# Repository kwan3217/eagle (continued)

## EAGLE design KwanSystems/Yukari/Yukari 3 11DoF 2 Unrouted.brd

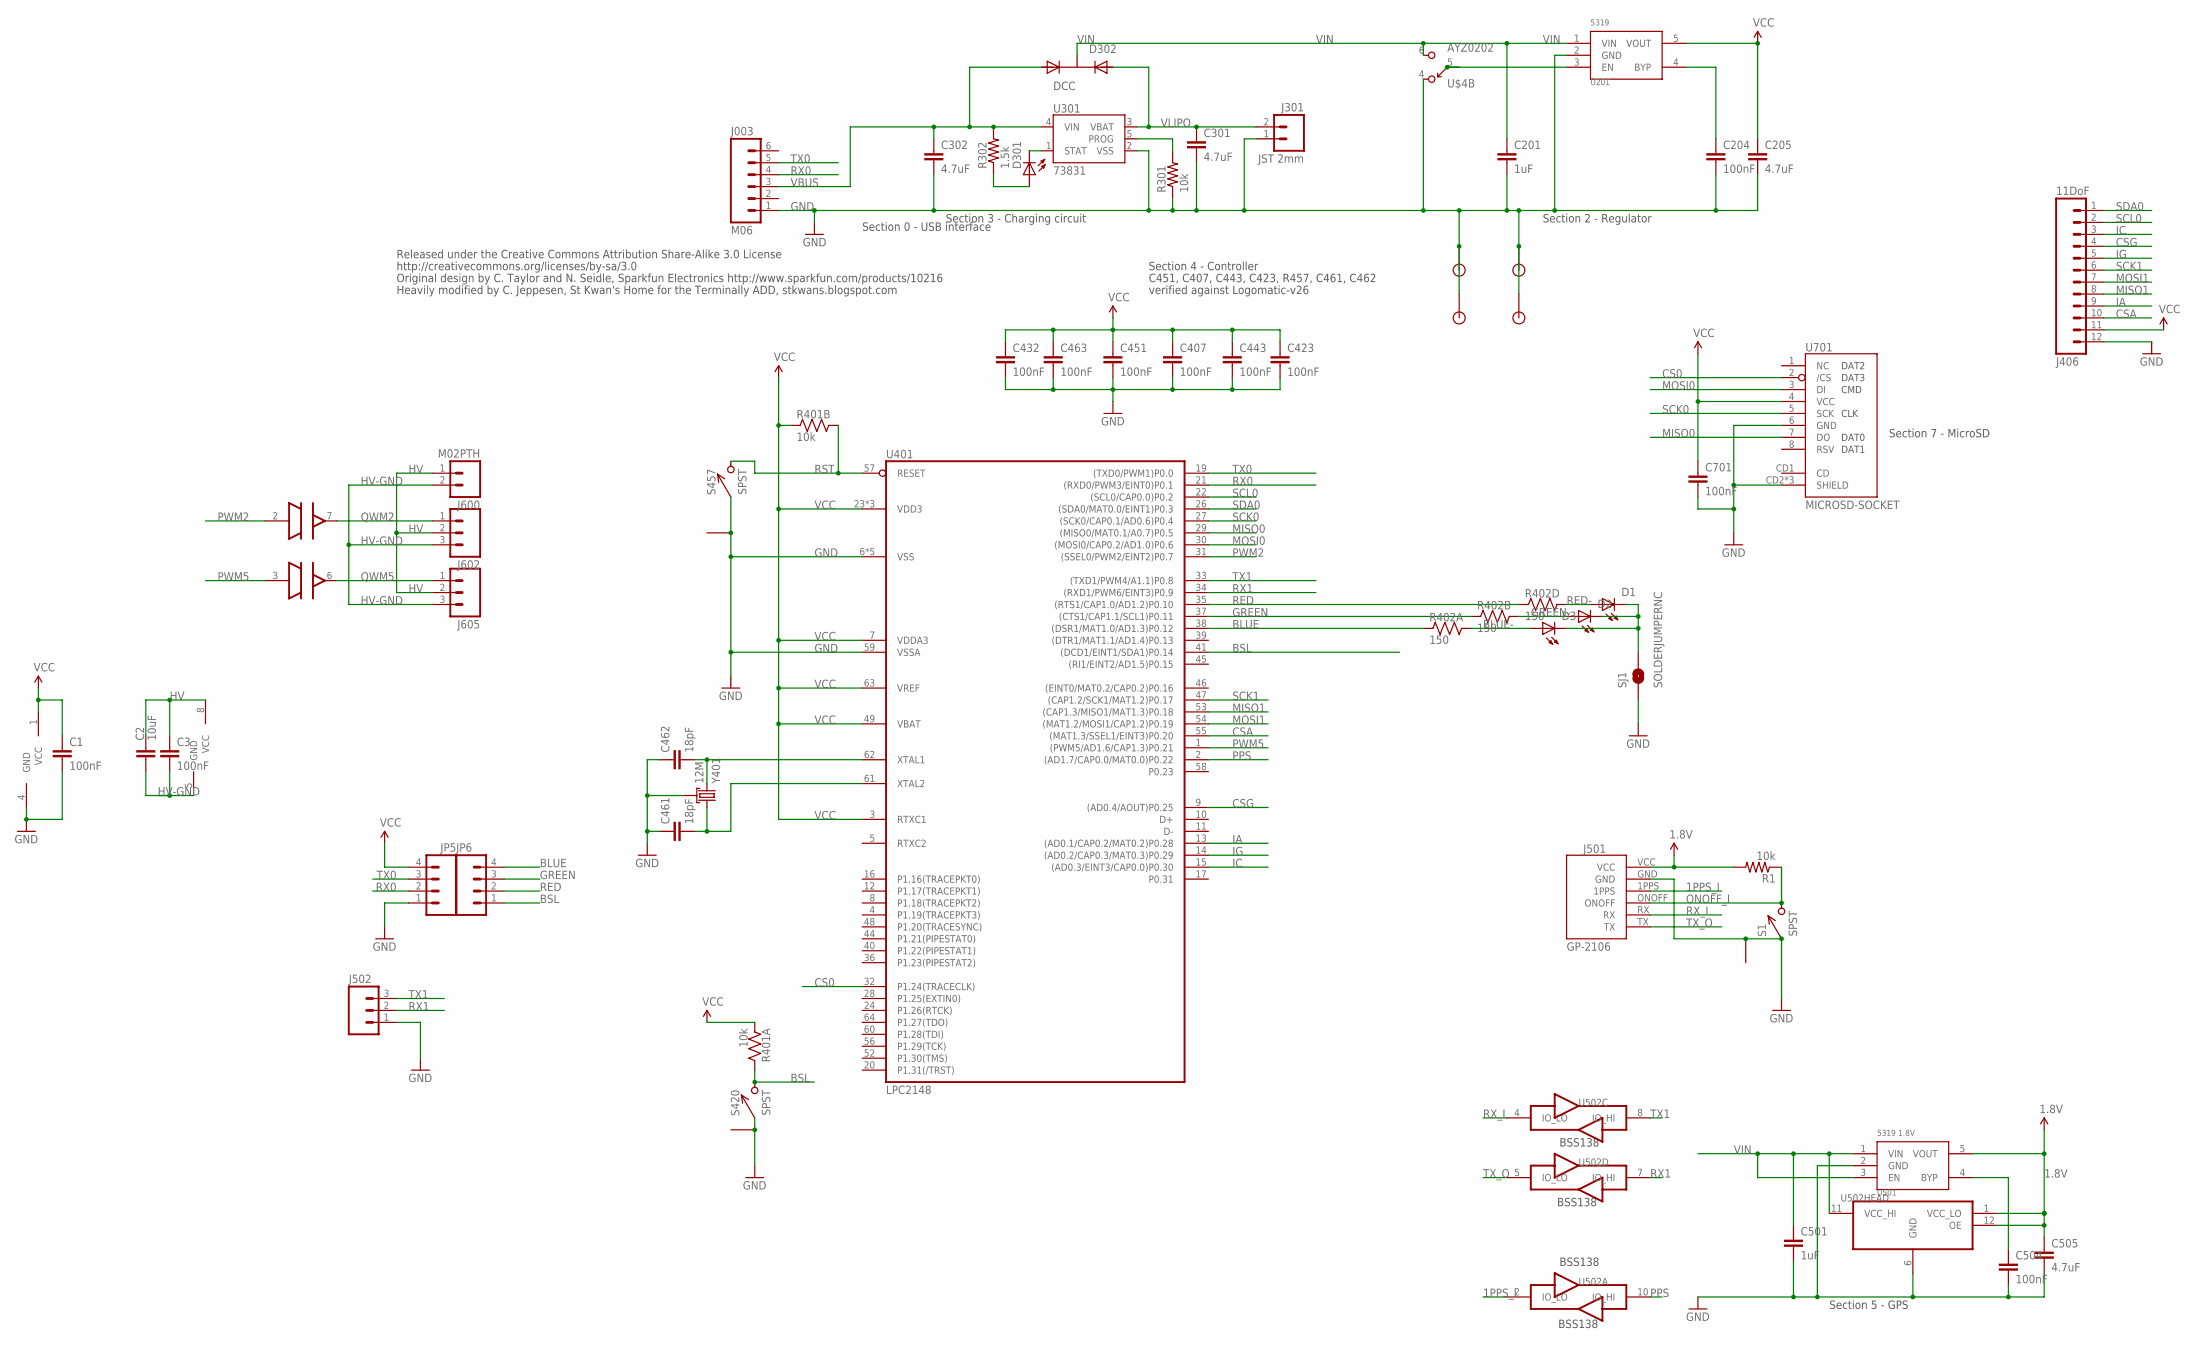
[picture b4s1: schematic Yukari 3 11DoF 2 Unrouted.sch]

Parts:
C1, C3, C204, C407, C423, C432, C443, C451, C463, C701: 100nF; 0402-CAP
C2: 10uF; 0603-CAP; DIGIKEY 445-7486-1-ND
C201: 1uF; 0402-CAP
C205, C301, C302: 4.7uF; 0402-CAP
C461, C462: 18pF; 0402-CAP
C501: 1uF; 0402-CAP; DIGIKEY 445-4114-1-ND
C504: 100nF; 0402-CAP; DIGIKEY 445-1265-1-ND
C505: 4.7uF; 0402-CAP; DIGIKEY 445-7395-1-ND
D1, D301: RED; LED-0603
D2: GREEN; LED-0603
D3: BLUE; LED-0603
D302: DCC; SOT-23-3
J003: M06; 1X06
J301: JST 2mm; JST-2-SMD
J406: 11DoF; 1X12
J501: GP-2106
J502, J602, J605: M03PTH; 1X03
J600: M02PTH; 1X02
JP1, JP2, JP3, JP4: STANDOFF
JP5, JP6: M04PTH; 1X04
R1, R301: 10k; 0402-RES
R302: 1.5k; 0402-RES
R401: 10k; CRA02
R402: 150; CRA04
S1, S420, S457: SPST; B3U-1100P
SJ1: SOLDERJUMPERNC; SJ_2S
U201: 5319; SOT-23-5
U301: 73831; SOT23-5
U401: LPC2148; LQFP64
U501: 5319 1.8V; SOT-23-5; DIGIKEY 576-1910-1-ND
U502: TXB0104RUT; R-PUQFN-N12
U600: ADUM3221; SO8N
U701: MICROSD-SOCKET; MICROSD-SOCKET-PP
U$4: AYZ0202
Y401: 12M; CRYSTAL_SMD

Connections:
1.8V: C505.1, J501.VCC, R1.2, U501.5 (VOUT), U502.1 (VCC_LO), U502.12 (OE)
1PPS_I: J501.1PPS, U502.2 (IO_LO)
BLUE: JP6.4, R402.1, U401.38 ((DSR1/MAT1.0/AD1.3)P0.12)
BLUE-: D3.A, R402.8 (2)
BSL: JP6.1, R401.4 (2), S420.P$2 (2), U401.41 ((DCD1/EINT1/SDA1)P0.14)
CHG_PROG: R301.2, U301.5 (PROG)
CS0: U401.32 (P1.24(TRACECLK)), U701.2 (/CS)
CSA: J406.10, U401.55 ((MAT1.3/SSEL1/EINT3)P0.20)
CSG: J406.4, U401.9 ((AD0.4/AOUT)P0.25)
EN: U201.3 (EN), U$4.5
GND: C1.2, C201.2, C204.2, C205.2, C301.2, C302.2, C407.2, C423.2, C432.2, C443.2, C451.2, C461.1, C462.1, C463.2, C501.2, C504.2, C505.2, C701.2, J003.1, J301.1, J406.12, J501.GND, J502.1, JP1.P$1, JP2.P$1, JP3.P$1, JP4.P$1, JP5.1, R301.1, S1.P$1 (1), S1.P$3 (1), S420.P$1 (1), S420.P$3 (1), S457.P$1 (1), S457.P$3 (1), SJ1.1, U201.2 (GND), U301.2 (VSS), U401.6 (VSS), U401.18 (VSS), U401.25 (VSS), U401.42 (VSS), U401.50 (VSS), U401.59 (VSSA), U501.2 (GND), U502.6 (GND), U600.4 (GND), U701.6 (GND), U701.CD2 (SHIELD), U701.GND1 (SHIELD), U701.GND3 (SHIELD), U$4.4, Y401.2 (GND), Y401.4 (GND)
GREEN: JP6.3, R402.2 (1), U401.37 ((CTS1/CAP1.1/SCL1)P0.11)
GREEN-: D2.A, R402.7 (2)
HV: C2.1, C3.1, J600.1, J602.2, J605.2, U600.8 (VCC)
HV-GND: C2.2, C3.2, J600.2, J602.3, J605.3, U600.5 (GND)
IA: J406.9, U401.13 ((AD0.1/CAP0.2/MAT0.2)P0.28)
IC: J406.3, U401.15 ((AD0.3/EINT3/CAP0.0)P0.30)
IG: J406.5, U401.14 ((AD0.2/CAP0.3/MAT0.3)P0.29)
MISO0: U401.29 ((MISO0/MAT0.1/A0.7)P0.5), U701.7 (DO)
MISO1: J406.8, U401.53 ((CAP1.3/MISO1/MAT1.3)P0.18)
MOSI0: U401.30 ((MOSI0/CAP0.2/AD1.0)P0.6), U701.3 (DI)
MOSI1: J406.7, U401.54 ((MAT1.2/MOSI1/CAP1.2)P0.19)
unnamed: D1.C, D2.C, D3.C, SJ1.2
unnamed: C504.1, U501.4 (BYP)
unnamed: C204.1, U201.4 (BYP)
ONOFF_I: J501.ONOFF, R1.1, S1.P$2 (2)
PPS: U401.2 ((AD1.7/CAP0.0/MAT0.0)P0.22), U502.10 (IO_HI)
PWM2: U401.31 ((SSEL0/PWM2/EINT2)P0.7), U600.2 (IN)
PWM5: U401.1 ((PWM5/AD1.6/CAP1.3)P0.21), U600.3 (IN)
QWM2: J602.1, U600.7 (OUT)
QWM5: J605.1, U600.6 (OUT)
RED: JP6.2, R402.4 (1), U401.35 ((RTS1/CAP1.0/AD1.2)P0.10)
RED-: D1.A, R402.5 (2)
RST: R401.3 (2), S457.P$2 (2), U401.57 (RESET)
RX0: J003.4, JP5.2, U401.21 ((RXD0/PWM3/EINT0)P0.1)
RX1: J502.2, U401.34 ((RXD1/PWM6/EINT3)P0.9), U502.7 (IO_HI)
RX_I: J501.RX, U502.4 (IO_LO)
SCK0: U401.27 ((SCK0/CAP0.1/AD0.6)P0.4), U701.5 (SCK)
SCK1: J406.6, U401.47 ((CAP1.2/SCK1/MAT1.2)P0.17)
SCL0: J406.2, U401.22 ((SCL0/CAP0.0)P0.2)
SDA0: J406.1, U401.26 ((SDA0/MAT0.0/EINT1)P0.3)
STAT+: D301.A, R302.1
STAT-: D301.C, U301.1 (STAT)
TX0: J003.5, JP5.3, U401.19 ((TXD0/PWM1)P0.0)
TX1: J502.3, U401.33 ((TXD1/PWM4/A1.1)P0.8), U502.8 (IO_HI)
TX_O: J501.TX, U502.5 (IO_LO)
VBUS: C302.1, D302.1 (A1), J003.3, R302.2, U301.4 (VIN)
VCC: C1.1, C205.1, C407.1, C423.1, C432.1, C443.1, C451.1, C463.1, C701.1, J406.11, JP5.4, R401.1, R401.2 (1), U201.5 (VOUT), U401.3 (RTXC1), U401.7 (VDDA3), U401.23 (VDD3), U401.43 (VDD3), U401.49 (VBAT), U401.51 (VDD3), U401.63 (VREF), U600.1 (VCC), U701.4 (VCC)
VIN: C201.1, C501.1, D302.3 (K), U201.1 (VIN), U501.1 (VIN), U501.3 (EN), U502.11 (VCC_HI), U$4.6
VLIPO: C301.1, D302.2 (A2), J301.2, U301.3 (VBAT)
XTAL1: C462.2, U401.62 (XTAL1), Y401.3 (2)
XTAL2: C461.2, U401.61 (XTAL2), Y401.1

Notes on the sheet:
Section 4 - Controller
Section 7 - MicroSD
C451, C407, C443, C423, R457, C461, C462
verified against Logomatic-v26
Section 2 - Regulator
Section 3 - Charging circuit
Section 0 - USB interface
Released under the Creative Commons Attribution Share-Alike 3.0 License
http://creativecommons.org/licenses/by-sa/3.0
Original design by C. Taylor and N. Seidle, Sparkfun Electronics http://www.sparkfun.com/products/10216
Heavily modified by C. Jeppesen, St Kwan's Home for the Terminally ADD, stkwans.blogspot.com
BSS138
Section 5 - GPS

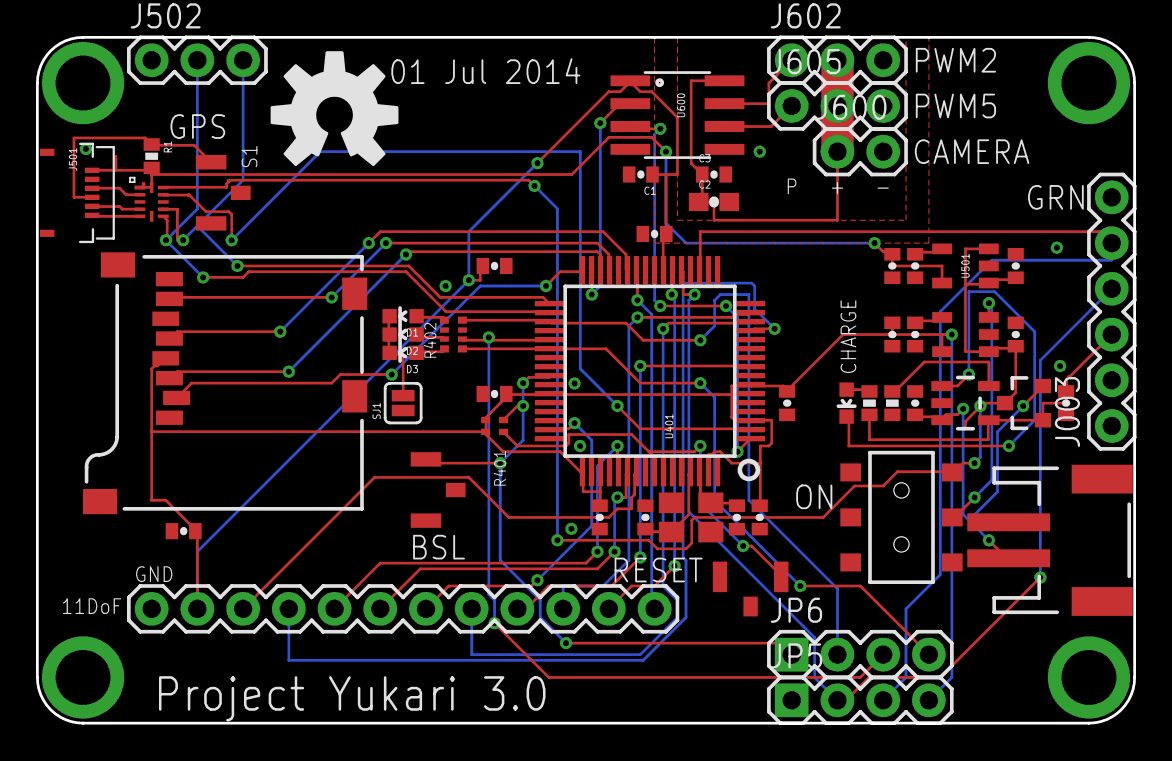
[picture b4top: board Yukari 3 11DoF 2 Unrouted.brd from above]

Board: 2 copper layers, 61.0 x 38.1 mm, 59 parts (1 on the bottom side), 52 nets.

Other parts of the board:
U$1: KWAN_CIRCLE
U$2: OSHW-LOGO-L

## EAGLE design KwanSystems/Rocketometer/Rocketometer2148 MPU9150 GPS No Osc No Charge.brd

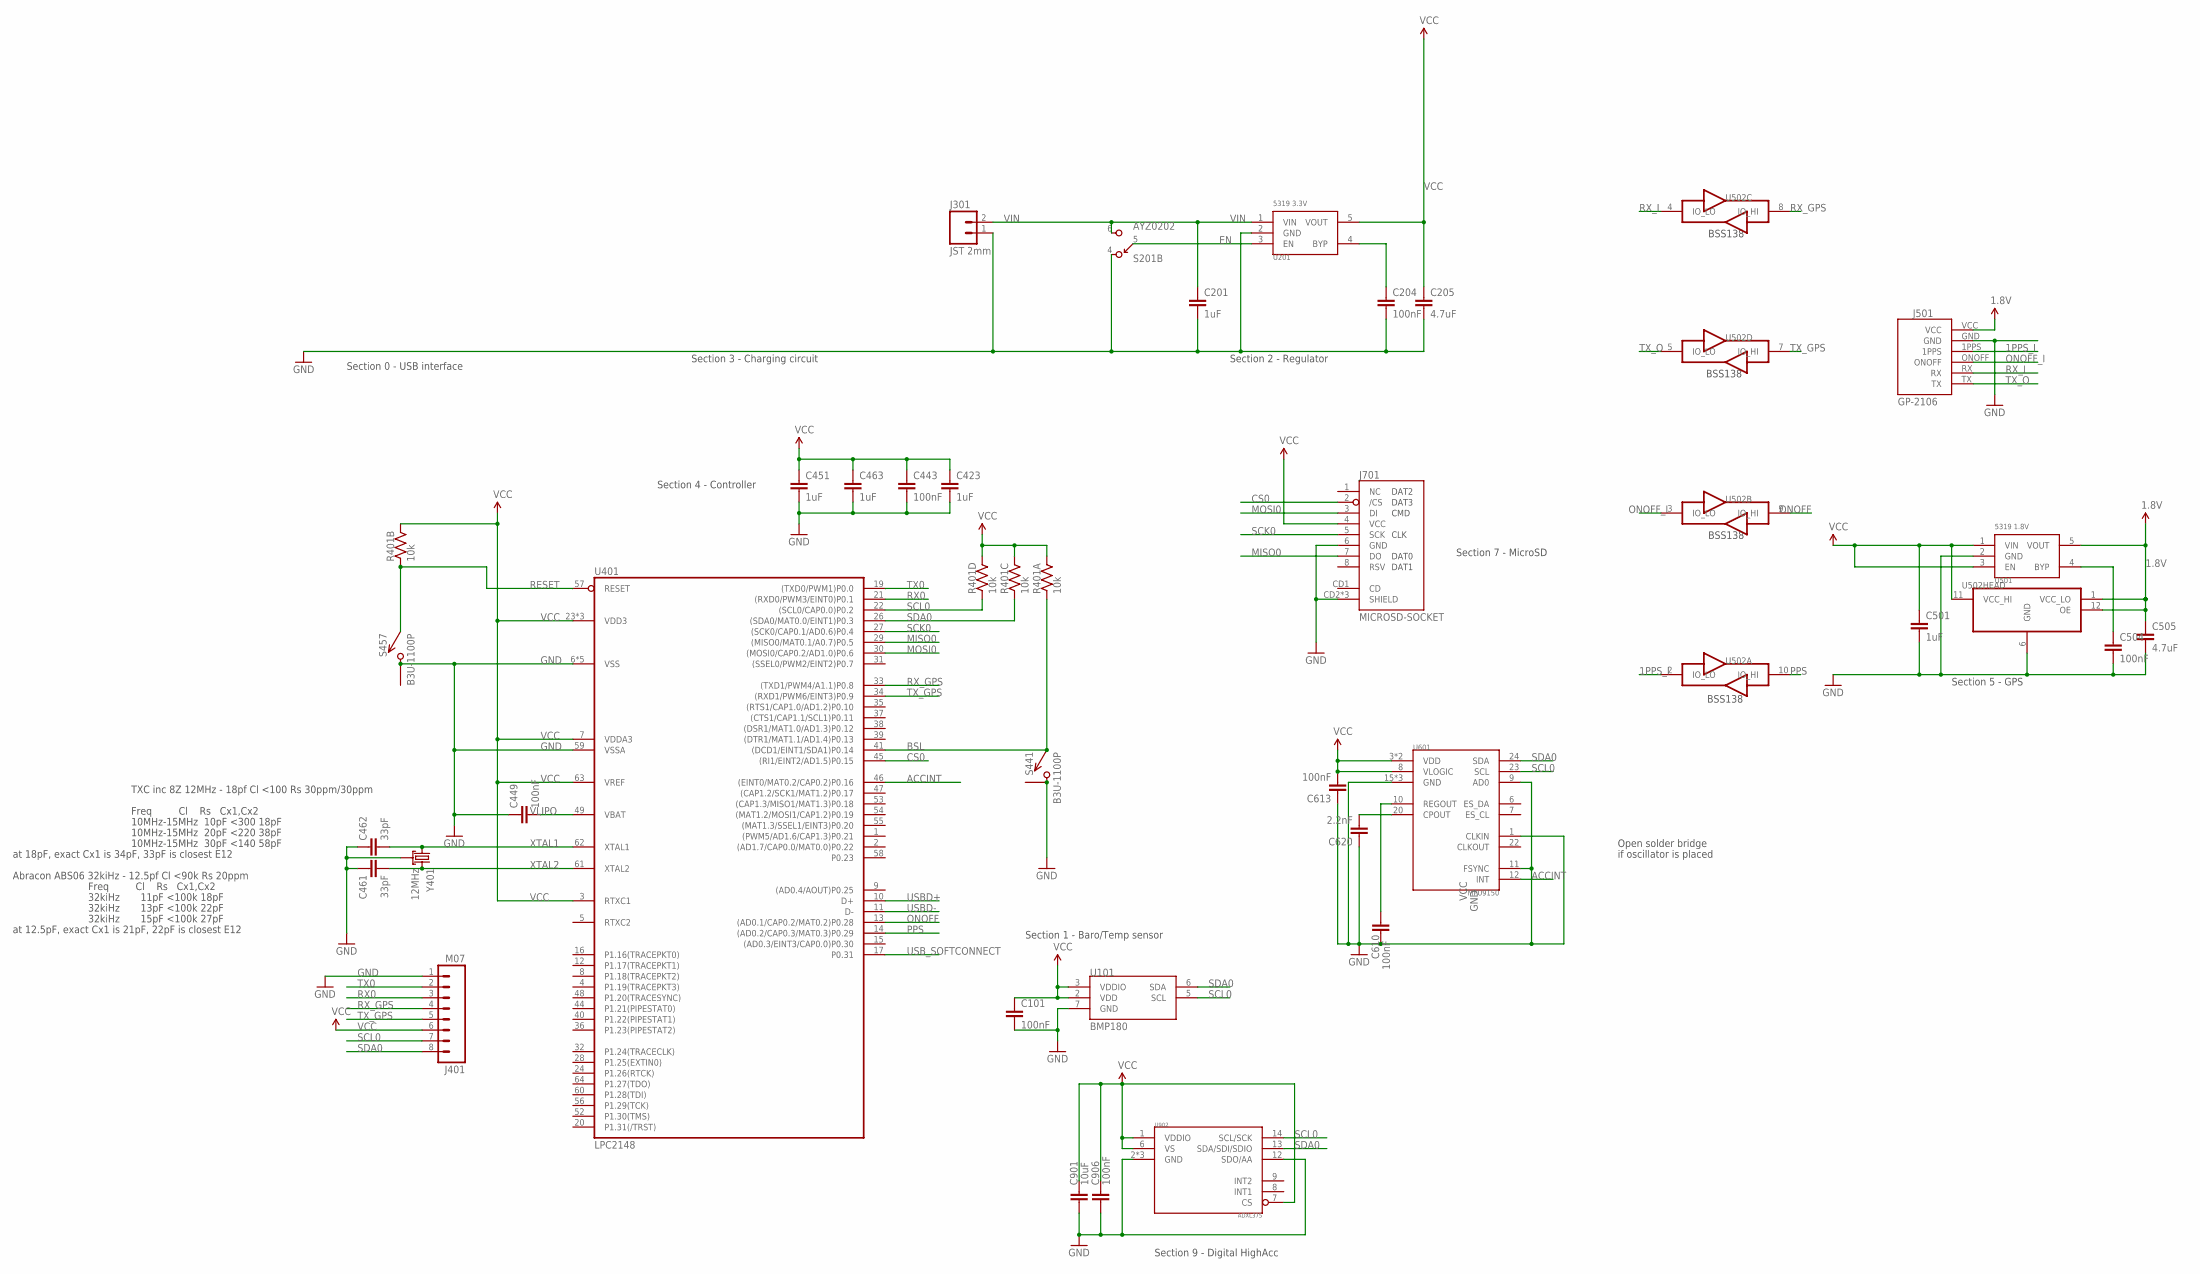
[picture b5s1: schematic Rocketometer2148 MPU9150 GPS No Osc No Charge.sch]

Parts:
C101, C204, C443, C449, C504, C610, C613, C906: 100nF; 0402-CAP; DIGIKEY 445-1265-1-ND
C201, C423, C451, C463, C501: 1uF; 0402-CAP; DIGIKEY 445-4114-1-ND
C205, C505: 4.7uF; 0402-CAP; DIGIKEY 445-7395-1-ND
C461, C462: 33pF; 0402-CAP; DIGIKEY 445-1241-1-ND
C620: 2.2nF; 0402-CAP; DIGIKEY 445-1257-1-ND
C901: 10uF; 0603-CAP; DIGIKEY 445-7486-1-ND
J301: JST 2mm; JST-2-SMD; DIGIKEY 455-1749-1-ND
J401: M07; 1X08; DIGIKEY $NOPART
J501: GP-2106
J701: MICROSD-SOCKET; MICROSD-SOCKET-PP; DIGIKEY 101-00581-59-1-ND
R401: 10k; CRA04; DIGIKEY CRA4S810KCT-ND
S201: AYZ0202; DIGIKEY 401-2013-1-ND
S441, S457: B3U-1100P; DIGIKEY SW1021CT-ND
U101: BMP180; DIGIKEY 828-1027-1-ND
U201: 5319 3.3V; SOT-23-5; DIGIKEY 576-1910-1-ND
U401: LPC2148; LQFP64
U501: 5319 1.8V; SOT-23-5; DIGIKEY 576-1910-1-ND
U502: TXB0104RUT; R-PUQFN-N12
U601: MPU9150; LLGA24; DIGIKEY $NOPART
U902: ADXL375; DIGIKEY ADXL375BCCZ-ND
Y401: 12MHz; CRYSTAL_SMD_2MM_2_5MM; DIGIKEY 887-1487-1-ND

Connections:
1.8V: C505.1, J501.VCC, U501.5 (VOUT), U502.1 (VCC_LO), U502.12 (OE)
1PPS_I: J501.1PPS, U502.2 (IO_LO)
ACCINT: U401.46 ((EINT0/MAT0.2/CAP0.2)P0.16), U601.12 (INT)
BSL: R401.1, S441.P$1 (1), U401.41 ((DCD1/EINT1/SDA1)P0.14)
CS0: J701.2 (/CS), U401.45 ((RI1/EINT2/AD1.5)P0.15)
EN: S201.5, U201.3 (EN)
GND: C101.2, C201.2, C204.2, C205.2, C423.2, C443.2, C449.1, C451.2, C461.1, C462.1, C463.2, C501.2, C504.2, C505.2, C610.2, C613.1, C620.1, C901.2, C906.2, J301.1, J401.1, J501.GND, J701.6 (GND), J701.CD2 (SHIELD), J701.GND1 (SHIELD), J701.GND3 (SHIELD), S201.4, S441.P$2 (2), S441.P$3 (1), S457.P$2 (2), S457.P$3 (1), U101.7 (GND), U201.2 (GND), U401.6 (VSS), U401.18 (VSS), U401.25 (VSS), U401.42 (VSS), U401.50 (VSS), U401.59 (VSSA), U501.2 (GND), U502.6 (GND), U601.1 (CLKIN), U601.9 (AD0), U601.11 (FSYNC), U601.15 (GND), U601.17 (GND), U601.18 (GND), U902.2 (GND), U902.4 (GND), U902.5 (GND), U902.12 (SDO/AA), Y401.2 (GND), Y401.4 (GND)
MISO0: J701.7 (DO), U401.29 ((MISO0/MAT0.1/A0.7)P0.5)
MOSI0: J701.3 (DI), U401.30 ((MOSI0/CAP0.2/AD1.0)P0.6)
unnamed: C620.2, U601.20 (CPOUT)
unnamed: C504.1, U501.4 (BYP)
unnamed: C610.1, U601.10 (REGOUT)
unnamed: C204.1, U201.4 (BYP)
ONOFF: U401.13 ((AD0.1/CAP0.2/MAT0.2)P0.28), U502.9 (IO_HI)
ONOFF_I: J501.ONOFF, U502.3 (IO_LO)
PPS: U401.14 ((AD0.2/CAP0.3/MAT0.3)P0.29), U502.10 (IO_HI)
RESET: R401.2 (1), S457.P$1 (1), U401.57 (RESET)
RX0: J401.3, U401.21 ((RXD0/PWM3/EINT0)P0.1)
RX_GPS: J401.4, U401.33 ((TXD1/PWM4/A1.1)P0.8), U502.8 (IO_HI)
RX_I: J501.RX, U502.4 (IO_LO)
SCK0: J701.5 (SCK), U401.27 ((SCK0/CAP0.1/AD0.6)P0.4)
SCL0: J401.7, R401.4 (1), U101.5 (SCL), U401.22 ((SCL0/CAP0.0)P0.2), U601.23 (SCL), U902.14 (SCL/SCK)
SDA0: J401.8, R401.3 (1), U101.6 (SDA), U401.26 ((SDA0/MAT0.0/EINT1)P0.3), U601.24 (SDA), U902.13 (SDA/SDI/SDIO)
TX0: J401.2, U401.19 ((TXD0/PWM1)P0.0)
TX_GPS: J401.5, U401.34 ((RXD1/PWM6/EINT3)P0.9), U502.7 (IO_HI)
TX_O: J501.TX, U502.5 (IO_LO)
USBD+: U401.10 (D+)
USBD-: U401.11 (D-)
USB_SOFTCONNECT: U401.17 (P0.31)
VCC: C101.1, C205.1, C423.1, C443.1, C451.1, C463.1, C501.1, C613.2, C901.1, C906.1, J401.6, J701.4 (VCC), R401.5 (2), R401.6 (2), R401.7 (2), R401.8 (2), U101.2 (VDD), U101.3 (VDDIO), U201.5 (VOUT), U401.3 (RTXC1), U401.7 (VDDA3), U401.23 (VDD3), U401.43 (VDD3), U401.51 (VDD3), U401.63 (VREF), U501.1 (VIN), U501.3 (EN), U502.11 (VCC_HI), U601.3 (VDD), U601.8 (VLOGIC), U601.13 (VDD), U902.1 (VDDIO), U902.6 (VS), U902.7 (CS)
VIN: C201.1, S201.6, U201.1 (VIN)
VLIPO: C449.2, U401.49 (VBAT)
XTAL1: C462.2, U401.62 (XTAL1), Y401.1
XTAL2: C461.2, U401.61 (XTAL2), Y401.3 (2)

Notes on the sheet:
Section 4 - Controller
Section 7 - MicroSD
Section 1 - Baro/Temp sensor
Freq Cl Rs Cx1,Cx2
10MHz-15MHz 10pF <300 18pF
10MHz-15MHz 20pF <220 38pF
10MHz-15MHz 30pF <140 58pF
TXC inc 8Z 12MHz - 18pf Cl <100 Rs 30ppm/30ppm
at 18pF, exact Cx1 is 34pF, 33pF is closest E12
32kiHz 11pF <100k 18pF
32kiHz 13pF <100k 22pF
32kiHz 15pF <100k 27pF
Abracon ABS06 32kiHz - 12.5pf Cl <90k Rs 20ppm
at 12.5pF, exact Cx1 is 21pF, 22pF is closest E12
Section 2 - Regulator
Section 3 - Charging circuit
Section 0 - USB interface
Open solder bridge
if oscillator is placed
Section 9 - Digital HighAcc
BSS138
Section 5 - GPS

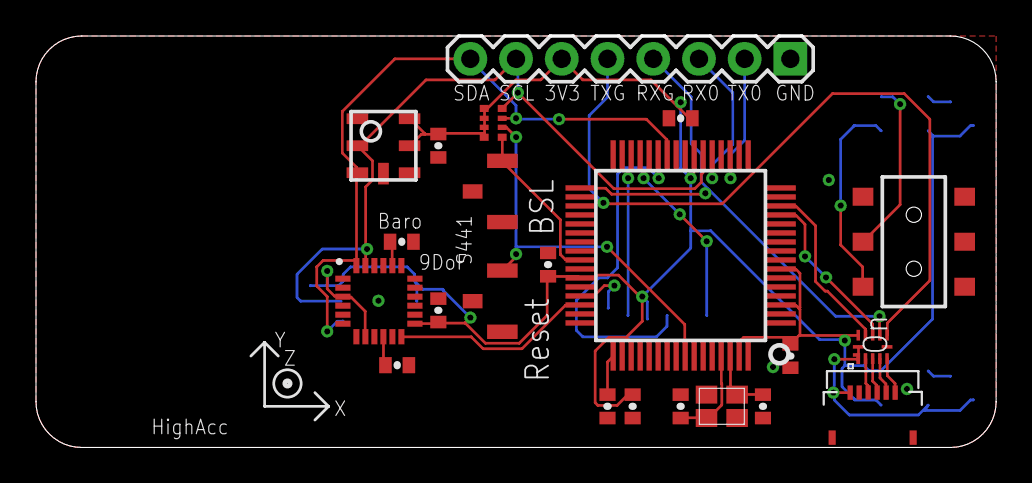
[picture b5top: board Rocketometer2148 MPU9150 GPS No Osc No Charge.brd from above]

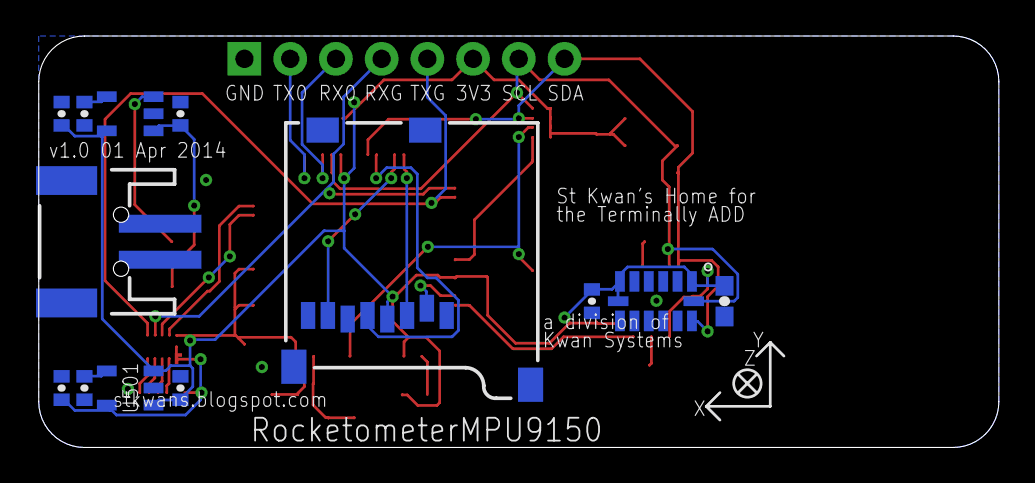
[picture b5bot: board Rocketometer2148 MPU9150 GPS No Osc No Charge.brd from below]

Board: 2 copper layers, 53.3 x 22.9 mm, 36 parts (13 on the bottom side), 31 nets.

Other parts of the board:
U$4: AXES

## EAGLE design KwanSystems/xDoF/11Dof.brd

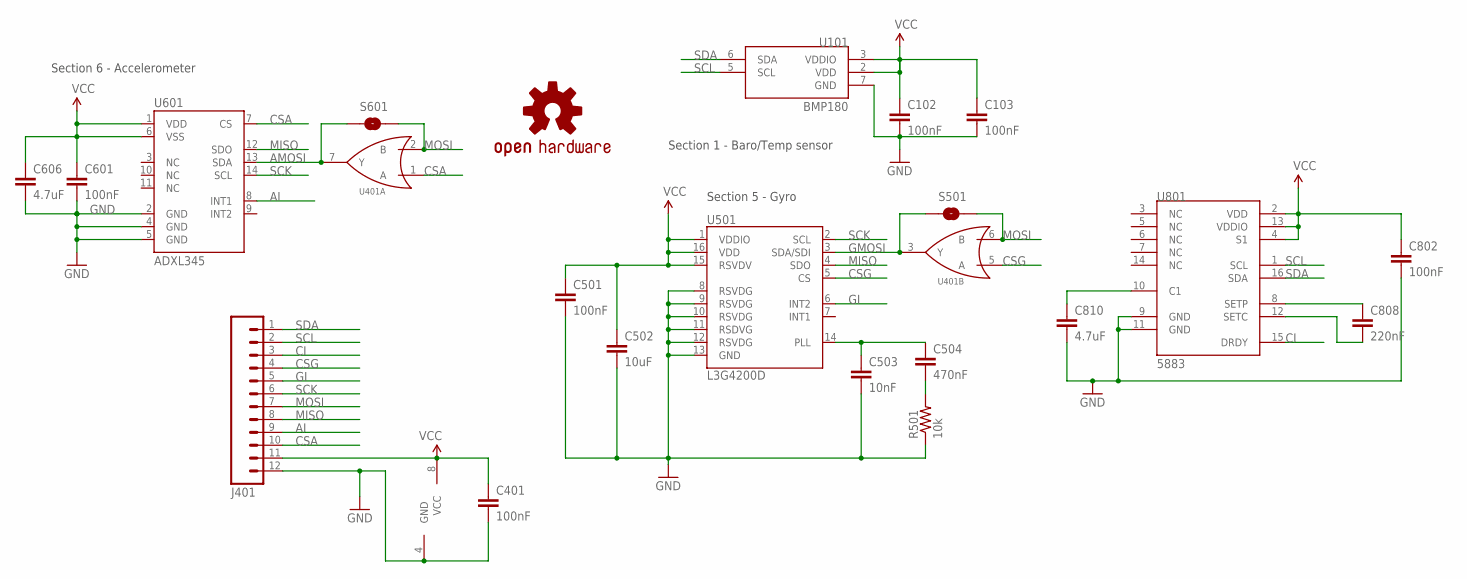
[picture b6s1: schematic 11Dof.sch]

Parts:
C102, C103, C401, C501, C601, C802: 100nF; 0603-CAP; DIGIKEY 445-1316-1-ND
C502: 10uF; 0603-CAP; DIGIKEY 445-7486-1-ND
C503: 10nF; 0603-CAP; DIGIKEY 445-1311-1-ND
C504: 470nF; 0603-CAP; DIGIKEY 445-5192-1-ND
C606, C810: 4.7uF; 0603-CAP; DIGIKEY 445-7483-1-ND
C808: 220nF; 0603-CAP; DIGIKEY 445-5132-1-ND
J401: M12PTH; 1X12; DIGIKEY $NOPART
R501: 10k; 0603-RES; DIGIKEY P10.0KHCT-ND
S501, S601: SOLDERJUMPERNO; SJ_2S-NO; DIGIKEY $NOPART
U101: BMP180; DIGIKEY 828-1027-1-ND
U401: 7432; DCU_8; DIGIKEY 296-13268-1-ND
U501: L3G4200D; LGA16-4X4; DIGIKEY 497-11071-1-ND
U601: ADXL345; LGA14; DIGIKEY ADXL345BCCZ-RL7CT-ND
U801: 5883; 16LPCC; DIGIKEY 342-1082-1-ND
U$2: OSHW-LOGOS; OSHW-LOGO-S; DIGIKEY $NOPART

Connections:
AI: J401.9, U601.8 (INT1)
AMOSI: S601.1, U401.7 (Y), U601.13 (SDA)
CI: J401.3, U801.15 (DRDY)
CSA: J401.10, U401.1 (A), U601.7 (CS)
CSG: J401.4, U401.5 (A), U501.5 (CS)
GI: J401.5, U501.6 (INT2)
GMOSI: S501.1, U401.3 (Y), U501.3 (SDA/SDI)
GND: C102.2, C103.2, C401.2, C501.2, C502.2, C503.2, C601.2, C606.2, C802.2, C810.2, J401.12, R501.1, U101.7 (GND), U401.4 (GND), U501.8 (RSVDG), U501.9 (RSVDG), U501.10 (RSVDG), U501.11 (RSDVG), U501.12 (RSVDG), U501.13 (GND), U601.2 (GND), U601.4 (GND), U601.5 (GND), U801.9 (GND), U801.11 (GND)
MISO: J401.8, U501.4 (SDO), U601.12 (SDO)
MOSI: J401.7, S501.2, S601.2, U401.2 (B), U401.6 (B)
unnamed: C503.1, C504.1, U501.14 (PLL)
unnamed: C504.2, R501.2
unnamed: C808.1, U801.8 (SETP)
unnamed: C808.2, U801.12 (SETC)
unnamed: C810.1, U801.10 (C1)
SCK: J401.6, U501.2 (SCL), U601.14 (SCL)
SCL: J401.2, U101.5 (SCL), U801.1 (SCL)
SDA: J401.1, U101.6 (SDA), U801.16 (SDA)
VCC: C102.1, C103.1, C401.1, C501.1, C502.1, C601.1, C606.1, C802.1, J401.11, U101.2 (VDD), U101.3 (VDDIO), U401.8 (VCC), U501.1 (VDDIO), U501.15 (RSVDV), U501.16 (VDD), U601.1 (VDD), U601.6 (VSS), U801.2 (VDD), U801.4 (S1), U801.13 (VDDIO)

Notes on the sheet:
Section 5 - Gyro
Section 6 - Accelerometer
Section 1 - Baro/Temp sensor

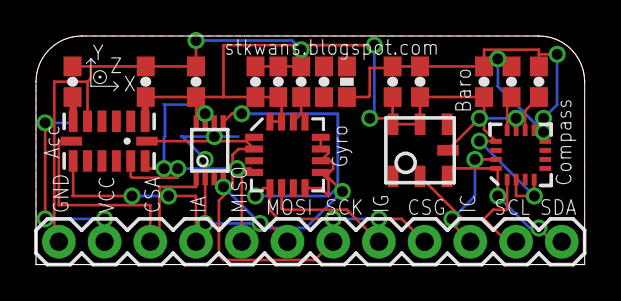
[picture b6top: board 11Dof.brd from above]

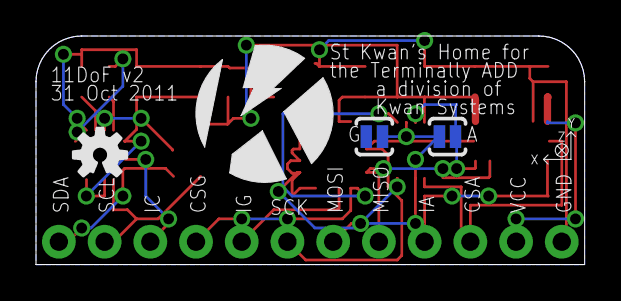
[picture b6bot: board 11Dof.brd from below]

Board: 2 copper layers, 30.5 x 12.7 mm, 23 parts (4 on the bottom side), 19 nets.

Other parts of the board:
U$1: KWAN_CIRCLE

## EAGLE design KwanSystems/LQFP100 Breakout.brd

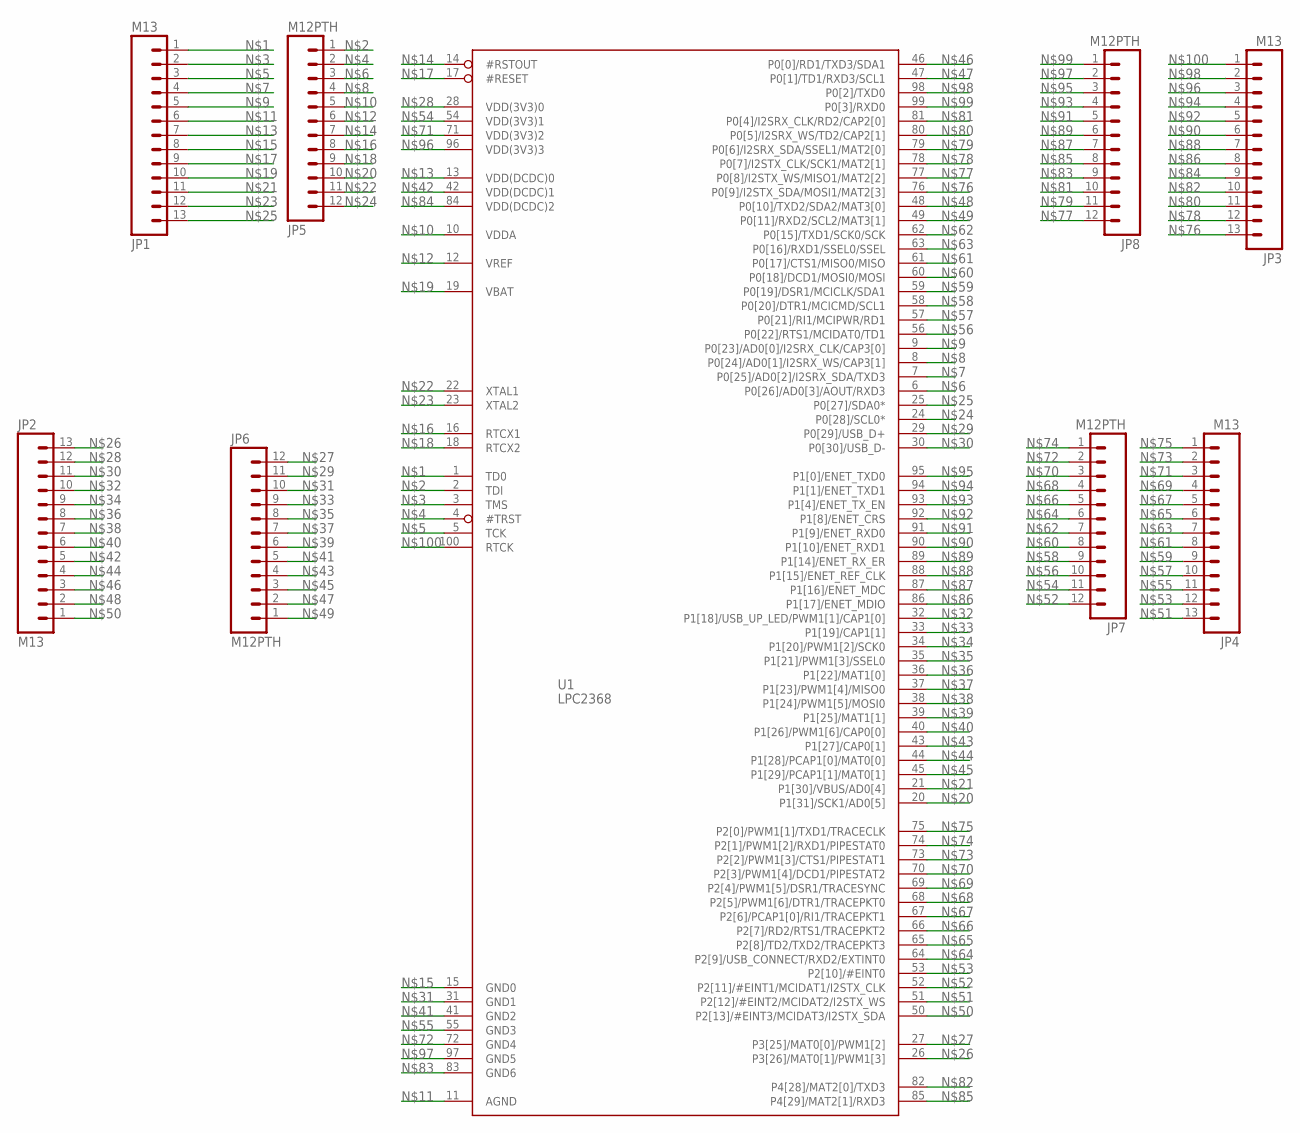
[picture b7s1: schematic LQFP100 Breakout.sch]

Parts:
JP1, JP2, JP3, JP4: M13; 1X13
JP5, JP6, JP7, JP8: M12PTH; 1X12
U1: LPC2368; LQFP100

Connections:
unnamed: JP1.1, U1.1 (TD0)
unnamed: JP5.1, U1.2 (TDI)
unnamed: JP1.2, U1.3 (TMS)
unnamed: JP5.2, U1.4 (#TRST)
unnamed: JP1.3, U1.5 (TCK)
unnamed: JP5.3, U1.6 (P0[26]/AD0[3]/AOUT/RXD3)
unnamed: JP1.4, U1.7 (P0[25]/AD0[2]/I2SRX_SDA/TXD3)
unnamed: JP5.4, U1.8 (P0[24]/AD0[1]/I2SRX_WS/CAP3[1])
unnamed: JP1.5, U1.9 (P0[23]/AD0[0]/I2SRX_CLK/CAP3[0])
unnamed: JP5.5, U1.10 (VDDA)
unnamed: JP1.6, U1.11 (AGND)
unnamed: JP5.6, U1.12 (VREF)
unnamed: JP1.7, U1.13 (VDD(DCDC)0)
unnamed: JP5.7, U1.14 (#RSTOUT)
unnamed: JP1.8, U1.15 (GND0)
unnamed: JP5.8, U1.16 (RTCX1)
unnamed: JP1.9, U1.17 (#RESET)
unnamed: JP5.9, U1.18 (RTCX2)
unnamed: JP1.10, U1.19 (VBAT)
unnamed: JP5.10, U1.20 (P1[31]/SCK1/AD0[5])
unnamed: JP1.11, U1.21 (P1[30]/VBUS/AD0[4])
unnamed: JP5.11, U1.22 (XTAL1)
unnamed: JP1.12, U1.23 (XTAL2)
unnamed: JP5.12, U1.24 (P0[28]/SCL0*)
unnamed: JP1.13, U1.25 (P0[27]/SDA0*)
unnamed: JP2.13, U1.26 (P3[26]/MAT0[1]/PWM1[3])
unnamed: JP6.12, U1.27 (P3[25]/MAT0[0]/PWM1[2])
unnamed: JP2.12, U1.28 (VDD(3V3)0)
unnamed: JP6.11, U1.29 (P0[29]/USB_D+)
unnamed: JP2.11, U1.30 (P0[30]/USB_D-)
unnamed: JP6.10, U1.31 (GND1)
unnamed: JP2.10, U1.32 (P1[18]/USB_UP_LED/PWM1[1]/CAP1[0])
unnamed: JP6.9, U1.33 (P1[19]/CAP1[1])
unnamed: JP2.9, U1.34 (P1[20]/PWM1[2]/SCK0)
unnamed: JP6.8, U1.35 (P1[21]/PWM1[3]/SSEL0)
unnamed: JP2.8, U1.36 (P1[22]/MAT1[0])
unnamed: JP6.7, U1.37 (P1[23]/PWM1[4]/MISO0)
unnamed: JP2.7, U1.38 (P1[24]/PWM1[5]/MOSI0)
unnamed: JP6.6, U1.39 (P1[25]/MAT1[1])
unnamed: JP2.6, U1.40 (P1[26]/PWM1[6]/CAP0[0])
unnamed: JP6.5, U1.41 (GND2)
unnamed: JP2.5, U1.42 (VDD(DCDC)1)
unnamed: JP6.4, U1.43 (P1[27]/CAP0[1])
unnamed: JP2.4, U1.44 (P1[28]/PCAP1[0]/MAT0[0])
unnamed: JP6.3, U1.45 (P1[29]/PCAP1[1]/MAT0[1])
unnamed: JP2.3, U1.46 (P0[0]/RD1/TXD3/SDA1)
unnamed: JP6.2, U1.47 (P0[1]/TD1/RXD3/SCL1)
unnamed: JP2.2, U1.48 (P0[10]/TXD2/SDA2/MAT3[0])
unnamed: JP6.1, U1.49 (P0[11]/RXD2/SCL2/MAT3[1])
unnamed: JP2.1, U1.50 (P2[13]/#EINT3/MCIDAT3/I2STX_SDA)
unnamed: JP4.13, U1.51 (P2[12]/#EINT2/MCIDAT2/I2STX_WS)
unnamed: JP7.12, U1.52 (P2[11]/#EINT1/MCIDAT1/I2STX_CLK)
unnamed: JP4.12, U1.53 (P2[10]/#EINT0)
unnamed: JP7.11, U1.54 (VDD(3V3)1)
unnamed: JP4.11, U1.55 (GND3)
unnamed: JP7.10, U1.56 (P0[22]/RTS1/MCIDAT0/TD1)
unnamed: JP4.10, U1.57 (P0[21]/RI1/MCIPWR/RD1)
unnamed: JP7.9, U1.58 (P0[20]/DTR1/MCICMD/SCL1)
unnamed: JP4.9, U1.59 (P0[19]/DSR1/MCICLK/SDA1)
unnamed: JP7.8, U1.60 (P0[18]/DCD1/MOSI0/MOSI)
unnamed: JP4.8, U1.61 (P0[17]/CTS1/MISO0/MISO)
unnamed: JP7.7, U1.62 (P0[15]/TXD1/SCK0/SCK)
unnamed: JP4.7, U1.63 (P0[16]/RXD1/SSEL0/SSEL)
unnamed: JP7.6, U1.64 (P2[9]/USB_CONNECT/RXD2/EXTINT0)
unnamed: JP4.6, U1.65 (P2[8]/TD2/TXD2/TRACEPKT3)
unnamed: JP7.5, U1.66 (P2[7]/RD2/RTS1/TRACEPKT2)
unnamed: JP4.5, U1.67 (P2[6]/PCAP1[0]/RI1/TRACEPKT1)
unnamed: JP7.4, U1.68 (P2[5]/PWM1[6]/DTR1/TRACEPKT0)
unnamed: JP4.4, U1.69 (P2[4]/PWM1[5]/DSR1/TRACESYNC)
unnamed: JP7.3, U1.70 (P2[3]/PWM1[4]/DCD1/PIPESTAT2)
unnamed: JP4.3, U1.71 (VDD(3V3)2)
unnamed: JP7.2, U1.72 (GND4)
unnamed: JP4.2, U1.73 (P2[2]/PWM1[3]/CTS1/PIPESTAT1)
unnamed: JP7.1, U1.74 (P2[1]/PWM1[2]/RXD1/PIPESTAT0)
unnamed: JP4.1, U1.75 (P2[0]/PWM1[1]/TXD1/TRACECLK)
unnamed: JP3.13, U1.76 (P0[9]/I2STX_SDA/MOSI1/MAT2[3])
unnamed: JP8.12, U1.77 (P0[8]/I2STX_WS/MISO1/MAT2[2])
unnamed: JP3.12, U1.78 (P0[7]/I2STX_CLK/SCK1/MAT2[1])
unnamed: JP8.11, U1.79 (P0[6]/I2SRX_SDA/SSEL1/MAT2[0])
unnamed: JP3.11, U1.80 (P0[5]/I2SRX_WS/TD2/CAP2[1])
unnamed: JP8.10, U1.81 (P0[4]/I2SRX_CLK/RD2/CAP2[0])
unnamed: JP3.10, U1.82 (P4[28]/MAT2[0]/TXD3)
unnamed: JP8.9, U1.83 (GND6)
unnamed: JP3.9, U1.84 (VDD(DCDC)2)
unnamed: JP8.8, U1.85 (P4[29]/MAT2[1]/RXD3)
unnamed: JP3.8, U1.86 (P1[17]/ENET_MDIO)
unnamed: JP8.7, U1.87 (P1[16]/ENET_MDC)
unnamed: JP3.7, U1.88 (P1[15]/ENET_REF_CLK)
unnamed: JP8.6, U1.89 (P1[14]/ENET_RX_ER)
unnamed: JP3.6, U1.90 (P1[10]/ENET_RXD1)
unnamed: JP8.5, U1.91 (P1[9]/ENET_RXD0)
unnamed: JP3.5, U1.92 (P1[8]/ENET_CRS)
unnamed: JP8.4, U1.93 (P1[4]/ENET_TX_EN)
unnamed: JP3.4, U1.94 (P1[1]/ENET_TXD1)
unnamed: JP8.3, U1.95 (P1[0]/ENET_TXD0)
unnamed: JP3.3, U1.96 (VDD(3V3)3)
unnamed: JP8.2, U1.97 (GND5)
unnamed: JP3.2, U1.98 (P0[2]/TXD0)
unnamed: JP8.1, U1.99 (P0[3]/RXD0)
unnamed: JP3.1, U1.100 (RTCK)

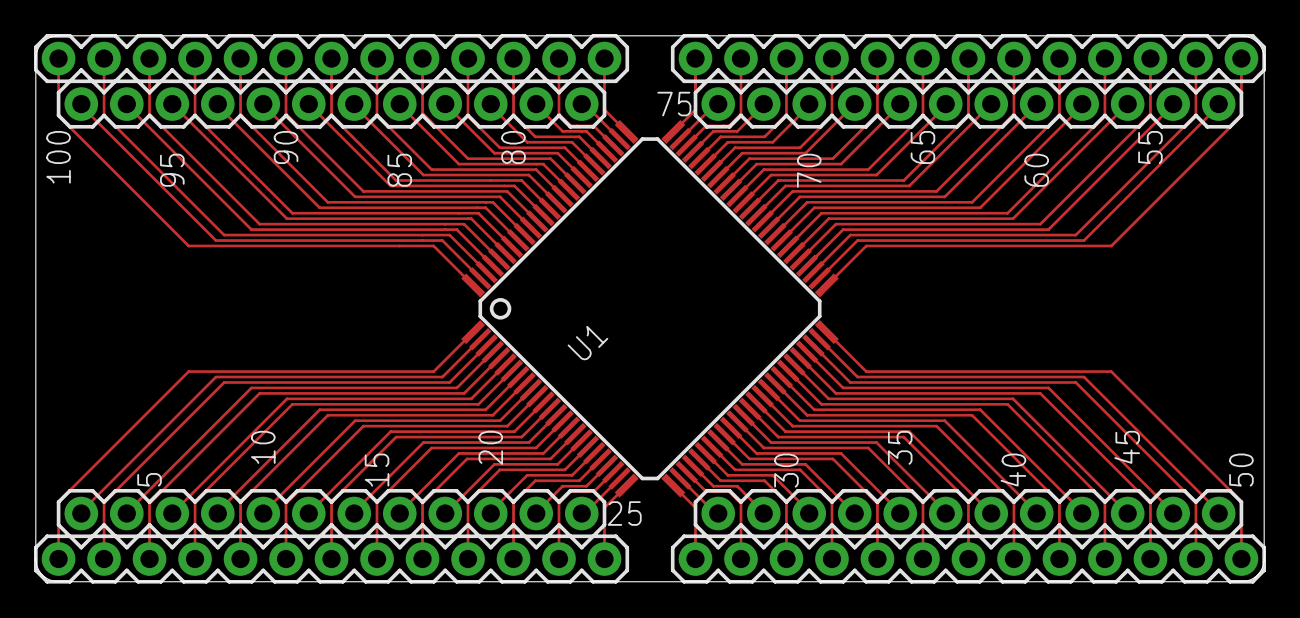
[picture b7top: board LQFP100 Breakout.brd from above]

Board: 2 copper layers, 68.6 x 30.5 mm, 9 parts (0 on the bottom side), 100 nets.
